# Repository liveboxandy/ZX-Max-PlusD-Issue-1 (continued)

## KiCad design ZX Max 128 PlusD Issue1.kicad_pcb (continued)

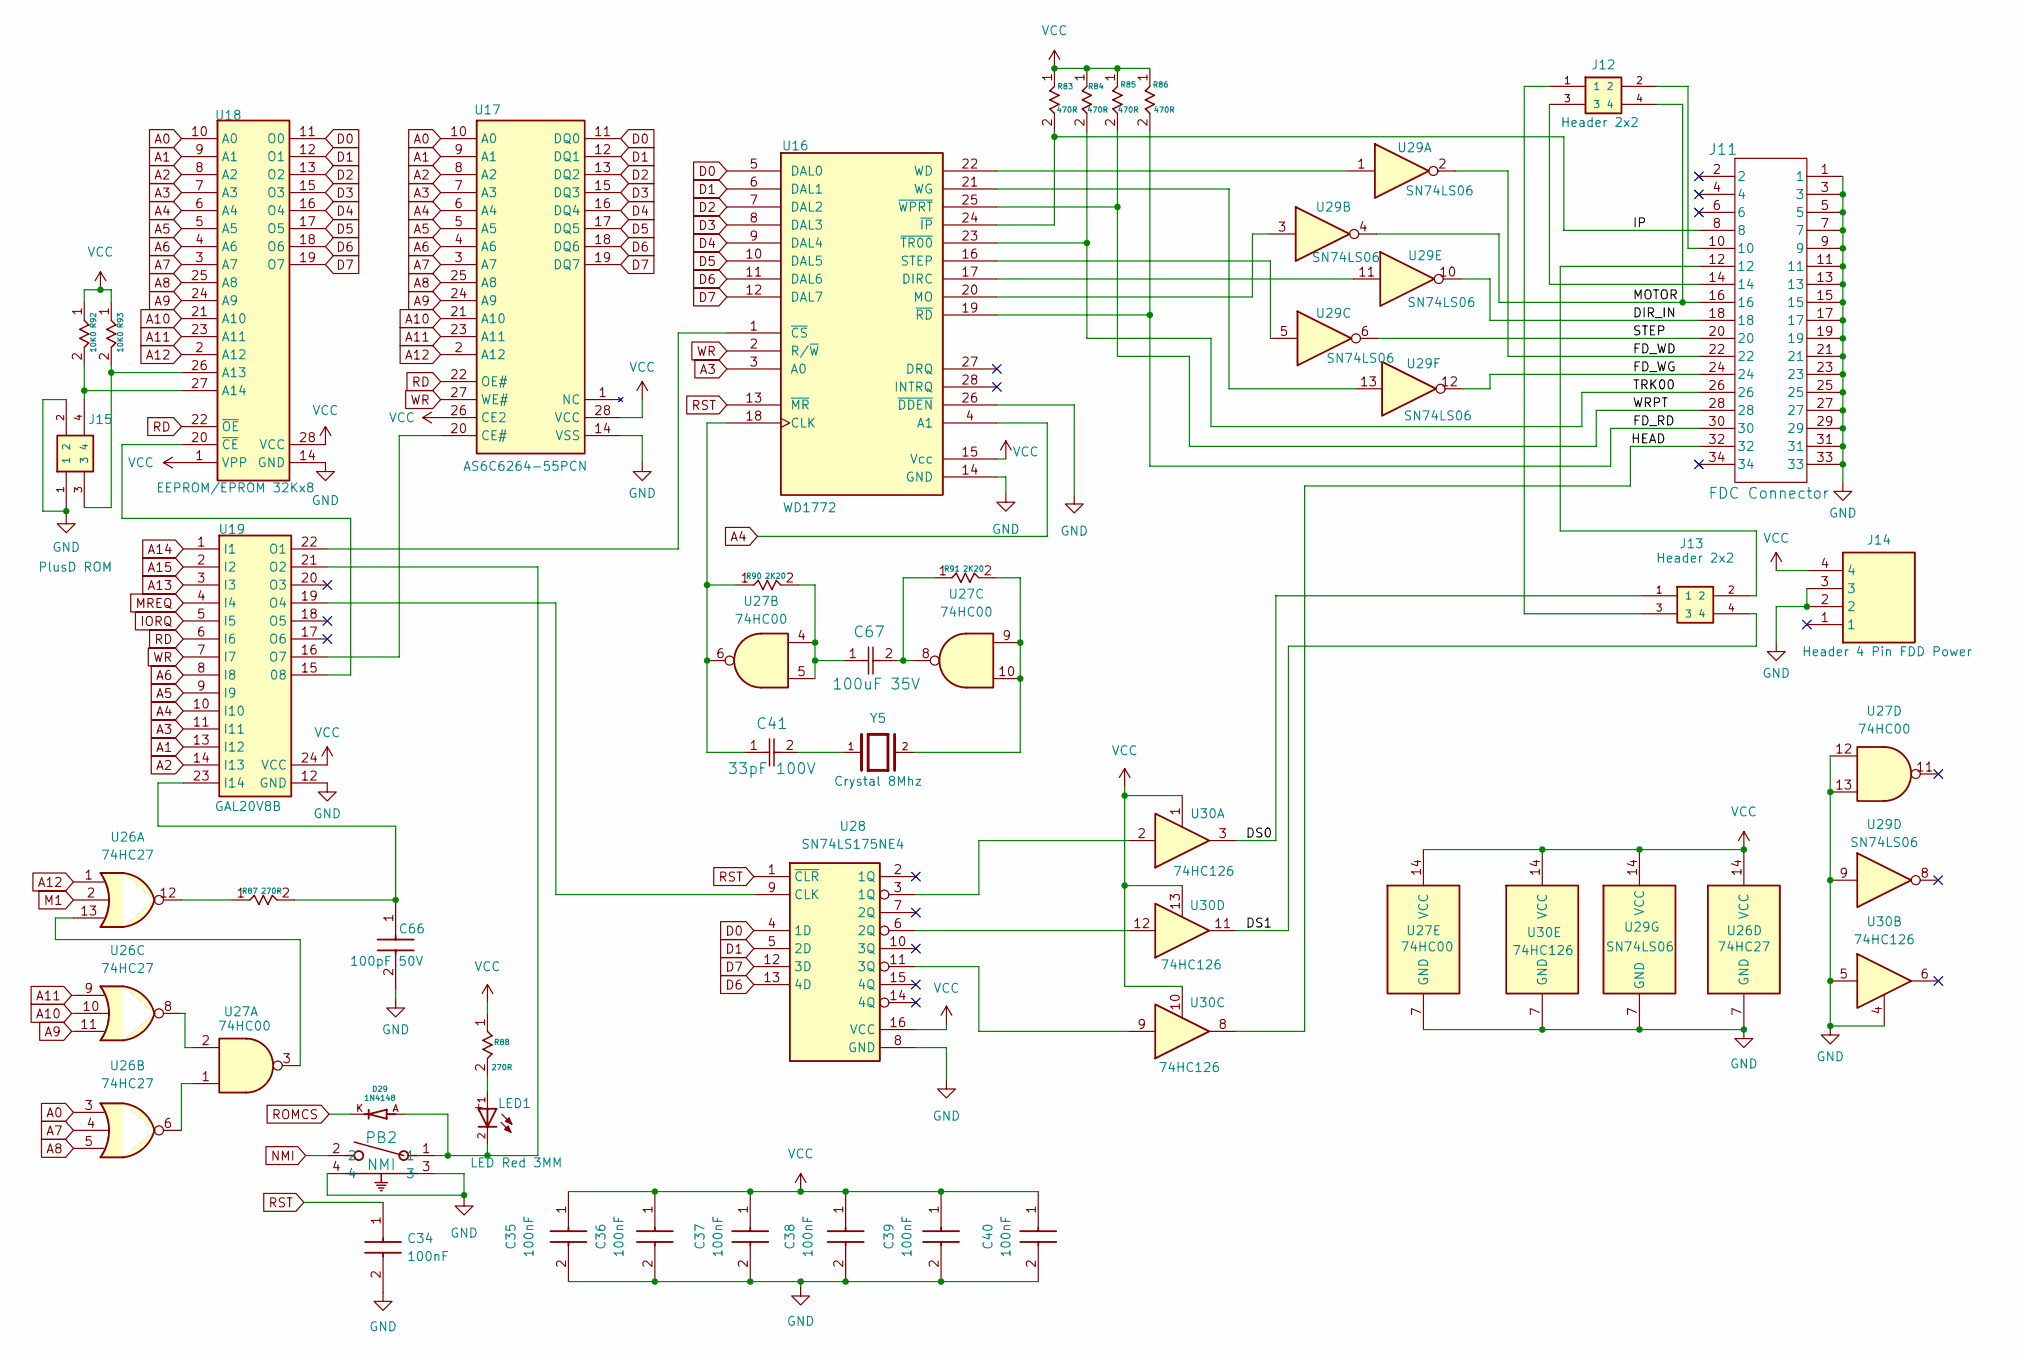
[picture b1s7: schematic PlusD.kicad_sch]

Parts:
C34, C35, C36, C37, C38, C39, C40: 100nF; CAPRB250W50L400T250H550; Mouser Part Number 594-K104Z15Y5VF5TL2
C41: 33pF 100V; K101J15C0GF53L2
C66: 100pF 50V; K101J15C0GF53L2
C67: 100uF 35V; CAP_YX_6P3X11_RUB
D29: 1N4148; DIOAD753W49L380D172B
J11: FDC Connector; CONN_5103311-7_TYC
J12, J13: Header 2x2; ADAM_PH2-04-UA
J14: Header 4 Pin FDD Power; HDRRA4W64P0X254_1X4_1016X320X610P
J15: PlusD ROM; ADAM_PH2-04-UA
LED1: LED Red 3MM; WL-TMRC_3MM
PB2: NMI; SW2_1825027-G_TEC
R83, R84, R85, R86: 470R; STA_CF14_STP
R87, R88: 270R; STA_CF14_STP
R90, R91: 2K20; STA_CF14_STP
R92, R93: 10K0; STA_CF14_STP
U16: WD1772; DIP1555W45P254L3733H482Q28
U17: AS6C6264-55PCN; DIP1555W45P254L3733H482Q28
U18: EEPROM/EPROM 32Kx8; DIP1556W56P254L3702H483Q28N
U19: GAL20V8B; DIP-24_W7.62mm_Socket
U26: 74HC27; DIP794W53P254L1930H508Q14N
U27: 74HC00; DIP794W53P254L1930H508Q14N
U28: SN74LS175NE4; DIP794W53P254L1930H508Q16N; Mouser Part Number 595-SN74LS175NE4
U29: SN74LS06; DIP794W53P254L1930H508Q14N
U30: 74HC126; DIP794W53P254L1930H508Q14N
Y5: Crystal 8Mhz; XTAL_HC49P488W43L1085T450H368

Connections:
/PlusD/DIR_IN: J11.18, U29.10
/PlusD/DS0: J13.1, U30.3
/PlusD/DS1: J13.4, U30.11
/PlusD/FD_RD: J11.30, R86.2, U16.19 (~RD)
/PlusD/FD_WD: J11.22, U29.2
/PlusD/FD_WG: J11.24, U29.12
/PlusD/HEAD: J11.32, U30.8
/PlusD/IP: J11.8, R83.2, U16.24 (~IP)
/PlusD/MOTOR: J11.16, J12.4, U29.4
/PlusD/STEP: J11.20, U29.6
/PlusD/TRK00: J11.26, R84.2, U16.23 (~TR00)
/PlusD/WRPT: J11.28, R85.2, U16.25 (~WPRT)
A0: U17.10 (A0), U18.10 (A0), U26.3; also elsewhere on the board
A1: U17.9 (A1), U18.9 (A1), U19.13 (I12); also elsewhere on the board
A2: U17.8 (A2), U18.8 (A2), U19.14 (I13); also elsewhere on the board
A3: U16.3 (A0), U17.7 (A3), U18.7 (A3), U19.11 (I11); also elsewhere on the board
A4: U16.4 (A1), U17.6 (A4), U18.6 (A4), U19.10 (I10); also elsewhere on the board
A5: U17.5 (A5), U18.5 (A5), U19.9 (I9); also elsewhere on the board
A6: U17.4 (A6), U18.4 (A6), U19.8 (I8); also elsewhere on the board
A7: U17.3 (A7), U18.3 (A7), U26.4; also elsewhere on the board
A8: U17.25 (A8), U18.25 (A8), U26.5; also elsewhere on the board
A9: U17.24 (A9), U18.24 (A9), U26.11; also elsewhere on the board
A10: U17.21 (A10), U18.21 (A10), U26.10; also elsewhere on the board
A11: U17.23 (A11), U18.23 (A11), U26.9; also elsewhere on the board
A12: U17.2 (A12), U18.2 (A12), U26.1; also elsewhere on the board
A13: U19.3 (I3); also elsewhere on the board
A14: U19.1 (I1); also elsewhere on the board
A15: U19.2 (I2); also elsewhere on the board
D0: U16.5 (DAL0), U17.11 (DQ0), U18.11 (O0), U28.4 (1D); also elsewhere on the board
D1: U16.6 (DAL1), U17.12 (DQ1), U18.12 (O1), U28.5 (2D); also elsewhere on the board
D2: U16.7 (DAL2), U17.13 (DQ2), U18.13 (O2); also elsewhere on the board
D3: U16.8 (DAL3), U17.15 (DQ3), U18.15 (O3); also elsewhere on the board
D4: U16.9 (DAL4), U17.16 (DQ4), U18.16 (O4); also elsewhere on the board
D5: U16.10 (DAL5), U17.17 (DQ5), U18.17 (O5); also elsewhere on the board
D6: U16.11 (DAL6), U17.18 (DQ6), U18.18 (O6), U28.13 (4D); also elsewhere on the board
D7: U16.12 (DAL7), U17.19 (DQ7), U18.19 (O7), U28.12 (3D); also elsewhere on the board
GND: C34.2 (-), C35.2 (-), C36.2 (-), C37.2 (-), C38.2 (-), C39.2 (-), C40.2 (-), C66.2, J11.1, J11.3, J11.5, J11.7, J11.9, J11.11, J11.13, J11.15, J11.17, J11.19, J11.21, J11.23, J11.25, J11.27, J11.29, J11.31, J11.33, J14.2, J14.3, J15.1, J15.2, PB2.3, PB2.4, U16.14 (GND), U16.26 (~DDEN), U17.14 (VSS), U18.14 (GND), U19.12 (GND), U26.7 (GND), U27.7 (GND), U27.12, U27.13, U28.8 (GND), U29.7 (GND), U29.9, U30.4, U30.5, U30.7 (GND); also elsewhere on the board
IORQ: U19.5 (I5); also elsewhere on the board
M1: U26.2; also elsewhere on the board
MREQ: U19.4 (I4); also elsewhere on the board
NMI: PB2.2; also elsewhere on the board
unnamed: C41.2, Y5.1
unnamed: C67.1, R90.2, U27.4, U27.5
unnamed: C67.2, R91.1, U27.8
unnamed: J11.10, J12.2
unnamed: J11.12, J13.2
unnamed: J11.14, J12.3
unnamed: J12.1, J13.3
unnamed: LED1.1, R88.2
unnamed: R87.1, U26.12
unnamed: R91.2, U27.9, U27.10, Y5.2
unnamed: C41.1, R90.1, U16.18 (CLK), U27.6
unnamed: U16.17 (DIRC), U29.11
unnamed: U16.20 (MO), U29.3
unnamed: U16.16 (STEP), U29.5
unnamed: U16.22 (WD), U29.1
unnamed: U16.21 (WG), U29.13
unnamed: U16.1 (~CS), U19.22 (O1)
unnamed: U17.20 (CE#), U19.16 (O7)
unnamed: J15.3, R93.2, U18.26 (A13)
unnamed: J15.4, R92.2, U18.27 (A14)
unnamed: U18.20 (~CE), U19.15 (08)
unnamed: C66.1, R87.2, U19.23 (I14)
unnamed: D29.A, LED1.2, PB2.1, U19.21 (O2)
unnamed: U19.19 (O4), U28.9 (CLK)
unnamed: U26.6, U27.1
unnamed: U26.8, U27.2
unnamed: U26.13, U27.3
unnamed: U28.3 (1Q), U30.2
unnamed: U28.6 (2Q), U30.12
unnamed: U28.11 (3Q), U30.9
RD: U17.22 (OE#), U18.22 (~OE), U19.6 (I6); also elsewhere on the board
ROMCS: D29.K; also elsewhere on the board
RST: C34.1 (+), U16.13 (~MR), U28.1 (~CLR); also elsewhere on the board
VCC: C35.1 (+), C36.1 (+), C37.1 (+), C38.1 (+), C39.1 (+), C40.1 (+), J14.4, R83.1, R84.1, R85.1, R86.1, R88.1, R92.1, R93.1, U16.15 (Vcc), U17.26 (CE2), U17.28 (VCC), U18.1 (VPP), U18.28 (VCC), U19.24 (VCC), U26.14 (VCC), U27.14 (VCC), U28.16 (VCC), U29.14 (VCC), U30.1, U30.10, U30.13, U30.14 (VCC); also elsewhere on the board
WR: U16.2 (R/~W), U17.27 (WE#), U19.7 (I7); also elsewhere on the board

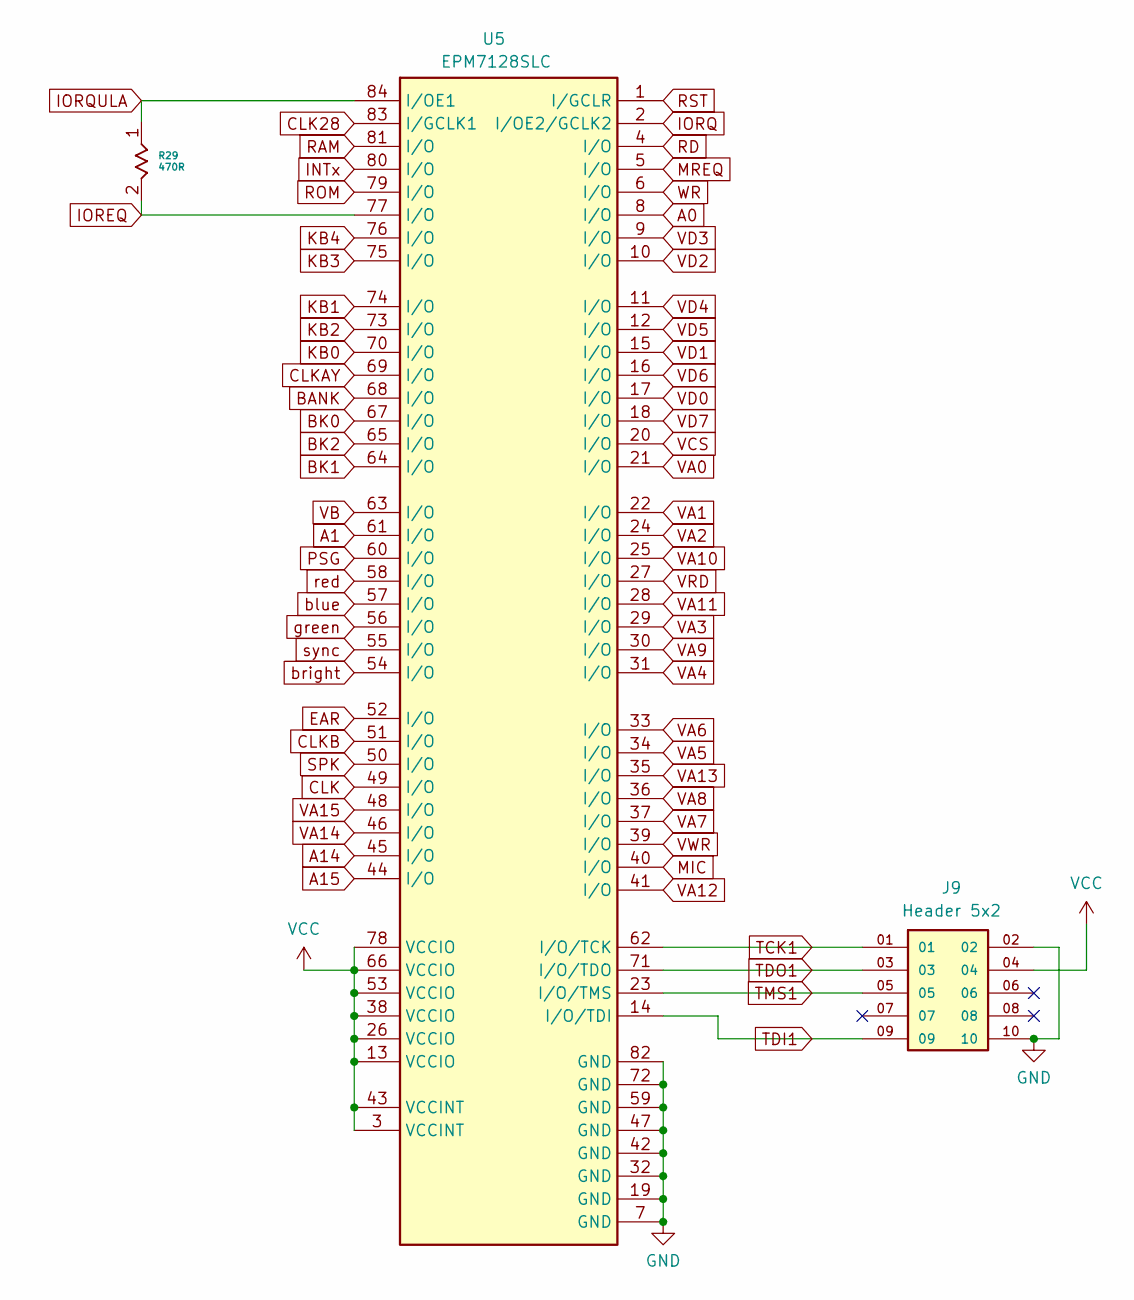
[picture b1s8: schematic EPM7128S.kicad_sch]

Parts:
J9: Header 5x2; AMPHENOL_10129381-910002BLF; PARTREV D
R29: 470R; STA_CF14_STP
U5: EPM7128SLC; PLCC84AT

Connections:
A0: U5.8 (I/O); also elsewhere on the board
A1: U5.61 (I/O); also elsewhere on the board
A14: U5.45 (I/O); also elsewhere on the board
A15: U5.44 (I/O); also elsewhere on the board
BANK: U5.68 (I/O); also elsewhere on the board
BK0: U5.67 (I/O); also elsewhere on the board
BK1: U5.64 (I/O); also elsewhere on the board
BK2: U5.65 (I/O); also elsewhere on the board
CLK: U5.49 (I/O); also elsewhere on the board
CLK28: U5.83 (I/GCLK1); also elsewhere on the board
CLKAY: U5.69 (I/O); also elsewhere on the board
CLKB: U5.51 (I/O); also elsewhere on the board
EAR: U5.52 (I/O); also elsewhere on the board
GND: J9.02, J9.10, U5.7 (GND), U5.19 (GND), U5.32 (GND), U5.42 (GND), U5.47 (GND), U5.59 (GND), U5.72 (GND), U5.82 (GND); also elsewhere on the board
INTx: U5.80 (I/O); also elsewhere on the board
IOREQ: R29.2, U5.77 (I/O)
IORQ: U5.2 (I/OE2/GCLK2); also elsewhere on the board
IORQULA: R29.1, U5.84 (I/OE1); also elsewhere on the board
KB0: U5.70 (I/O); also elsewhere on the board
KB1: U5.74 (I/O); also elsewhere on the board
KB2: U5.73 (I/O); also elsewhere on the board
KB3: U5.75 (I/O); also elsewhere on the board
KB4: U5.76 (I/O); also elsewhere on the board
MIC: U5.40 (I/O); also elsewhere on the board
MREQ: U5.5 (I/O); also elsewhere on the board
PSG: U5.60 (I/O); also elsewhere on the board
RAM: U5.81 (I/O); also elsewhere on the board
RD: U5.4 (I/O); also elsewhere on the board
ROM: U5.79 (I/O); also elsewhere on the board
RST: U5.1 (I/GCLR); also elsewhere on the board
SPK: U5.50 (I/O); also elsewhere on the board
TCK1: J9.01, U5.62 (I/O/TCK)
TDI1: J9.09, U5.14 (I/O/TDI)
TDO1: J9.03, U5.71 (I/O/TDO)
TMS1: J9.05, U5.23 (I/O/TMS)
VA0: U5.21 (I/O); also elsewhere on the board
VA1: U5.22 (I/O); also elsewhere on the board
VA2: U5.24 (I/O); also elsewhere on the board
VA3: U5.29 (I/O); also elsewhere on the board
VA4: U5.31 (I/O); also elsewhere on the board
VA5: U5.34 (I/O); also elsewhere on the board
VA6: U5.33 (I/O); also elsewhere on the board
VA7: U5.37 (I/O); also elsewhere on the board
VA8: U5.36 (I/O); also elsewhere on the board
VA9: U5.30 (I/O); also elsewhere on the board
VA10: U5.25 (I/O); also elsewhere on the board
VA11: U5.28 (I/O); also elsewhere on the board
VA12: U5.41 (I/O); also elsewhere on the board
VA13: U5.35 (I/O); also elsewhere on the board
VA14: U5.46 (I/O); also elsewhere on the board
VA15: U5.48 (I/O); also elsewhere on the board
VB: U5.63 (I/O); also elsewhere on the board
VCC: J9.04, U5.3 (VCCINT), U5.13 (VCCIO), U5.26 (VCCIO), U5.38 (VCCIO), U5.43 (VCCINT), U5.53 (VCCIO), U5.66 (VCCIO), U5.78 (VCCIO); also elsewhere on the board
VCS: U5.20 (I/O); also elsewhere on the board
VD0: U5.17 (I/O); also elsewhere on the board
VD1: U5.15 (I/O); also elsewhere on the board
VD2: U5.10 (I/O); also elsewhere on the board
VD3: U5.9 (I/O); also elsewhere on the board
VD4: U5.11 (I/O); also elsewhere on the board
VD5: U5.12 (I/O); also elsewhere on the board
VD6: U5.16 (I/O); also elsewhere on the board
VD7: U5.18 (I/O); also elsewhere on the board
VRD: U5.27 (I/O); also elsewhere on the board
VWR: U5.39 (I/O); also elsewhere on the board
WR: U5.6 (I/O); also elsewhere on the board
blue: U5.57 (I/O); also elsewhere on the board
bright: U5.54 (I/O); also elsewhere on the board
green: U5.56 (I/O); also elsewhere on the board
red: U5.58 (I/O); also elsewhere on the board
sync: U5.55 (I/O); also elsewhere on the board

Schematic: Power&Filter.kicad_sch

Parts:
C4: 10uF 25V; CAPPRD200W50D500H1100; Mouser Part Number 667-ECA-1EM100B
C5: 22uF 16V; CAPPRD200W50D500H1100; Mouser Part Number 667-ECA-1EM100B
C8: 220uF 16V; CAPPRD200W50D500H1100
C9, C10, C11, C12, C13, C14, C15, C16, C17, C19, C20: 100nF; CAPRB250W50L400T250H550; Mouser Part Number 594-K104Z15Y5VF5TL2
D28: DF02M; DIP825W58P510L832H543Q4N; Mouser Part Number 621-DF02M
J3: ZX_48K_EDGE; ZX_BUS_B_TOP
J4: PJ-002A; CUI_PJ-002A
J17: Header 2x1; HARWIN_M20-9990246; PARTREV 14
U14: R-78E5.0-1.0; CONV_R-78E5.0-1.0; PARTREV 6

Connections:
+9V: C4.1 (+), D28.1 (+), J3.A4 (+9), U14.1 (+VIN)
+12V: J3.B22 (+12)
-5V: J3.B20 (-5)
-12V: J3.B23 (-12)
A0: J3.A9 (A0); also elsewhere on the board
A1: J3.A10 (A1); also elsewhere on the board
A2: J3.A11 (A2); also elsewhere on the board
A3: J3.A12 (A3); also elsewhere on the board
A4: J3.A24 (A4); also elsewhere on the board
A5: J3.A23 (A5); also elsewhere on the board
A6: J3.A22 (A6); also elsewhere on the board
A7: J3.A21 (A7); also elsewhere on the board
A8: J3.B26 (A8); also elsewhere on the board
A9: J3.A27 (A9); also elsewhere on the board
A10: J3.B27 (A10); also elsewhere on the board
A11: J3.A28 (A11); also elsewhere on the board
A12: J3.A2 (A12); also elsewhere on the board
A13: J3.B2 (A13); also elsewhere on the board
A14: J3.A1 (A14); also elsewhere on the board
A15: J3.B1 (A15); also elsewhere on the board
BUSAK: J3.A26 (BUSACK); also elsewhere on the board
BUSRQ: J3.A19 (BUSRQ); also elsewhere on the board
CLKB: J3.A8 (CLOCK); also elsewhere on the board
D0: J3.B6 (D0); also elsewhere on the board
D1: J3.B7 (D1); also elsewhere on the board
D2: J3.B8 (D2); also elsewhere on the board
D3: J3.B11 (D3); also elsewhere on the board
D4: J3.B12 (D4); also elsewhere on the board
D5: J3.B10 (D5); also elsewhere on the board
D6: J3.B9 (D6); also elsewhere on the board
D7: J3.B3 (D7); also elsewhere on the board
GND: C4.2 (-), C5.2 (-), C8.2, C9.2 (-), C10.2 (-), C11.2 (-), C12.2 (-), C13.2 (-), C14.2 (-), C15.2 (-), C16.2 (-), C17.2 (-), C19.2 (-), C20.2 (-), D28.2 (-), J3.A6 (GND), J3.A7 (GND), J3.A14 (GND), J17.2, U14.2 (GND); also elsewhere on the board
HALT: J3.B15 (HALT); also elsewhere on the board
INT: J3.B13 (INT); also elsewhere on the board
IORQ: J3.B17 (IOREQ); also elsewhere on the board
IORQULA: J3.A13 (IORQGE); also elsewhere on the board
M1: J3.B24 (M1); also elsewhere on the board
MREQ: J3.B16 (MREQ); also elsewhere on the board
NMI: J3.B14 (NMI); also elsewhere on the board
unnamed: D28.3 (~_1), J4.1
unnamed: D28.4 (~_2), J4.2, J4.3
RD: J3.B18 (RD); also elsewhere on the board
RFSH: J3.B25 (RFSH); also elsewhere on the board
ROMCS: J3.A25 (ROMCS); also elsewhere on the board
RST: J3.A20 (RESET); also elsewhere on the board
VCC: C5.1 (+), C8.1, C9.1 (+), C10.1 (+), C11.1 (+), C12.1 (+), C13.1 (+), C14.1 (+), C15.1 (+), C16.1 (+), C17.1 (+), C19.1 (+), C20.1 (+), J3.A3 (+5), J17.1, U14.3 (+VOUT); also elsewhere on the board
WAIT: J3.B21 (WAIT); also elsewhere on the board
WR: J3.B19 (WR); also elsewhere on the board

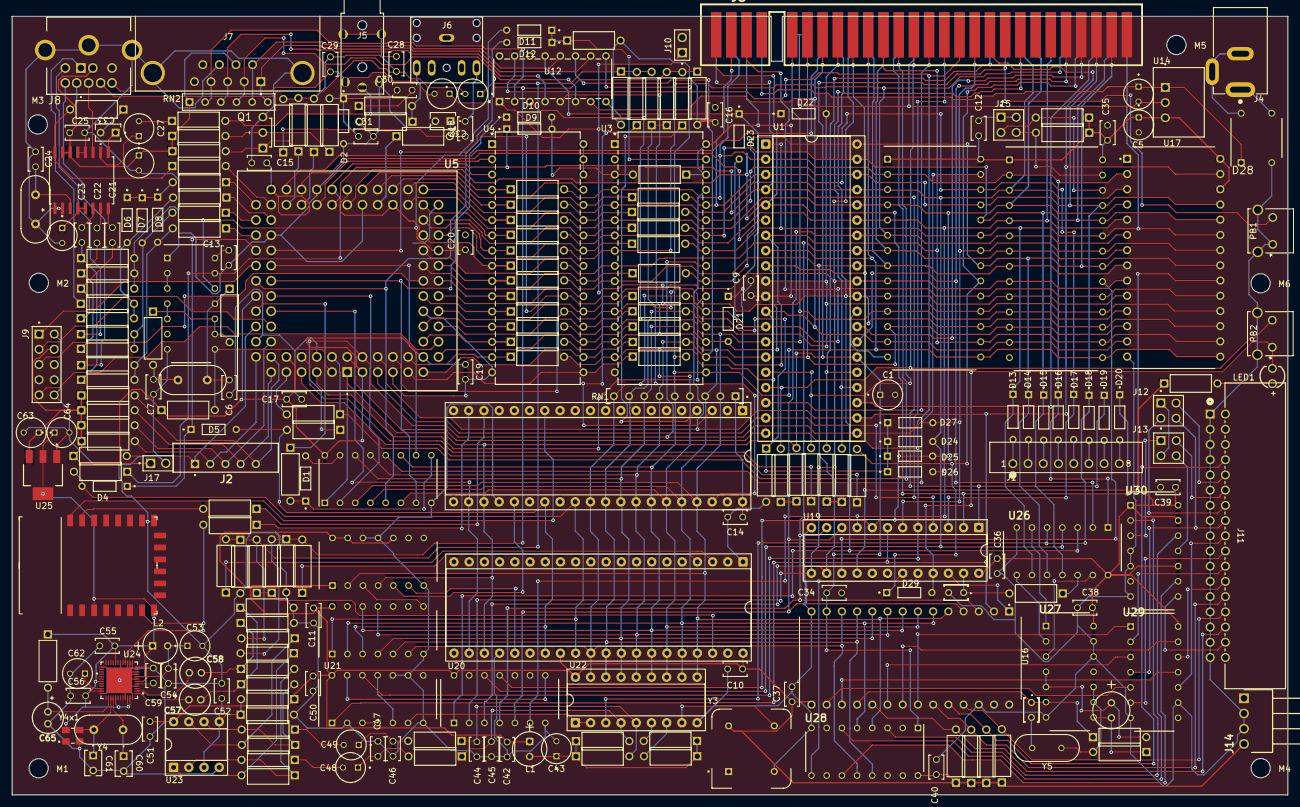
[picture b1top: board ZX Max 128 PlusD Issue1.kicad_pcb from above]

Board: 2 copper layers, 213.0 x 130.0 mm, 272 parts (0 on the bottom side), 248 nets.

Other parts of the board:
C2, C3: 10uF 25V; CAPPRD200W50D500H1100
D4, D5: 1N4148; DIOAD753W49L380D172B
J5: AV Jack; PJ-322A
R57, R58, R81, R82: 470R; STA_CF14_STP
R59, R62, R63, R64, R65, R68, R69, R70: 1K00; STA_CF14_STP
R60, R61, R66, R67: 2K20; STA_CF14_STP
U8, U9: AY-3-8910; Z80_Socket
U10: CD74HC30E; DIP794W53P254L1930H508Q14N
U11: 74HC74; DIP794W53P254L1930H508Q14N
U15: ESP8266-12E; WIFI_Module_ESP8266_12E

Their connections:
+3V3D: U15.3 (EN), U15.8 (VCC); also elsewhere on the board
A14: R57.1; also elsewhere on the board
A-AY: R59.1, U8.4 (CHANNEL_A)
A-AY2: R65.1, U9.4 (CHANNEL_A)
AY1: U8.25 (A8), U11.5 (Q)
AY2: U9.25 (A8), U11.6 (~Q)
Audio-L: C3.2 (-), J5.3; also elsewhere on the board
Audio-R: C2.2 (-), J5.4; also elsewhere on the board
B-AY: R62.1, U8.3 (CHANNEL_B)
B-AY2: R68.1, U9.3 (CHANNEL_B)
BC1: D4.A, R57.2, U8.29 (BC1), U9.29 (BC1), U10.1
BDIR: D5.A, R58.2, U8.27 (BDIR), U9.27 (BDIR), U10.3
C-AY: R60.1, R61.1, U8.38 (CHANNEL_C)
CLKAY: U8.22 (CLK), U9.22 (CLK); also elsewhere on the board
Comp: J5.1; also elsewhere on the board
D0: U8.37 (DA0), U9.37 (DA0), U11.2 (D); also elsewhere on the board
D1: U8.36 (DA1), U9.36 (DA1), U10.2; also elsewhere on the board
D2: U8.35 (DA2), U9.35 (DA2); also elsewhere on the board
D3: U8.34 (DA3), U9.34 (DA3), U10.12; also elsewhere on the board
D4: U8.33 (DA4), U9.33 (DA4), U10.11; also elsewhere on the board
D5: U8.32 (DA5), U9.32 (DA5), U10.4; also elsewhere on the board
D6: U8.31 (DA6), U9.31 (DA6), U10.5; also elsewhere on the board
D7: U8.30 (DA7), U9.30 (DA7), U10.6; also elsewhere on the board
GND: J5.2, R63.2, R64.2, R69.2, R70.2, U8.1 (VSS), U8.24 (~A9), U9.1 (VSS), U9.24 (~A9), U10.7 (GND), U11.7 (GND), U11.11 (C), U11.12 (D), U15.15 (GND), U15.16 (TXD2/IO15); also elsewhere on the board
IN4: U8.14 (IOA7), U15.22 (TXD0/TXD)
L-in: C3.1 (+), R61.2, R62.2, R64.1, R67.2, R68.2, R70.1; also elsewhere on the board
MIDI: R81.2, U15.7 (MOSI/IO13); also elsewhere on the board
unnamed: R66.1, R67.1, U9.38 (CHANNEL_C)
unnamed: U10.8, U11.3 (C)
unnamed: R82.2, U15.21 (RXD0/RXD)
OUT3: R81.1, U8.19 (IOA2)
OUT4: R82.1, U8.18 (IOA3)
PSG: D4.K, D5.K; also elsewhere on the board
R-in: C2.1 (+), R59.2, R60.2, R63.1, R65.2, R66.2, R69.1; also elsewhere on the board
RD: R58.1; also elsewhere on the board
RST: U8.23 (~RESET), U9.23 (~RESET), U11.4 (~S); also elsewhere on the board
VCC: U8.28 (BC2), U8.40 (VCC), U9.28 (BC2), U9.40 (VCC), U10.14 (VCC), U11.1 (~R), U11.10 (~S), U11.13 (~R), U11.14 (VCC); also elsewhere on the board

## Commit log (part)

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2026-02-05 Initial upload of KiCAD 9 files for ZX Max PlusD Issue 1 PCB
    Initial upload of KiCAD 9 files for ZX Max PlusD Issue 1 PCB, Folders for BOM, MOD, STEP and SYM to follow.
2026-02-05 Add files via upload
    Initial upload of KiCAD 9 files for ZX Max PlusD Issue 1 PCB, Folders for BOM and MOD. STEP and SYM to follow.
2026-02-05 Add files via upload
    Initial upload of KiCAD 9 files for ZX Max PlusD Issue 1 PCB, Folder for SYM. STEP to follow.
2026-02-05 Add files via upload
    Initial upload of KiCAD 9 files for ZX Max PlusD Issue 1 PCB, Folder STEP part 1.
2026-02-05 Add files via upload
    Initial upload of KiCAD 9 files for ZX Max PlusD Issue 1 PCB, Folder STEP part 2.
2026-02-05 Add README with project overview and warnings
    Added a README file with project details and warnings about PCB layout accuracy.
2026-02-05 Fix typos and improve wording in README.md
2026-02-06 Delete Step directory
    Appears Step files from Samtec are not allowed to be shared.
